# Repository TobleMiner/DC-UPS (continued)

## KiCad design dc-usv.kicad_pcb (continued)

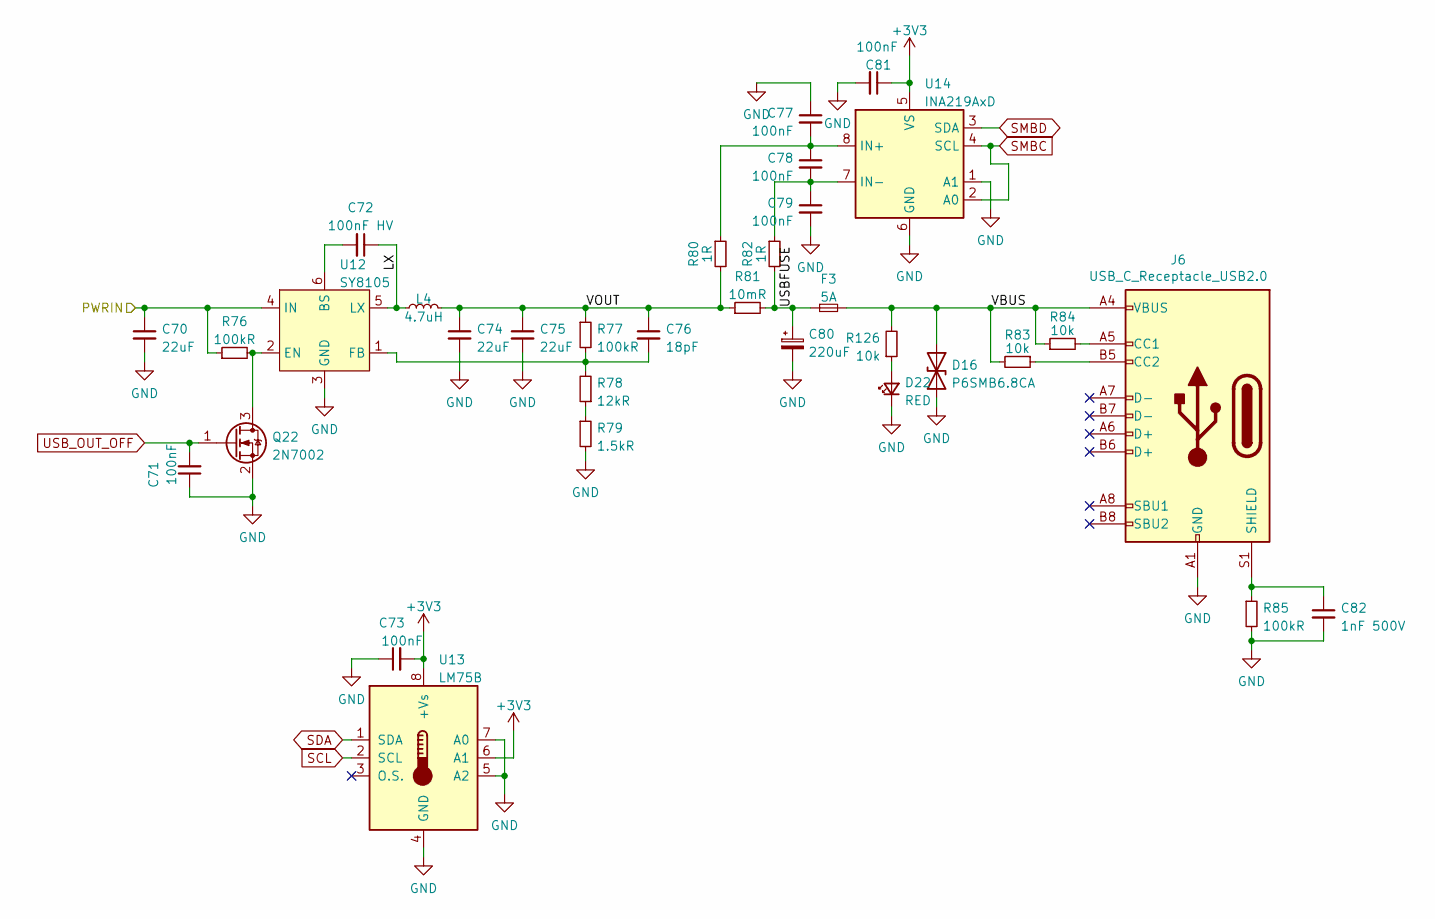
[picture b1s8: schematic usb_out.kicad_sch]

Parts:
C70, C74, C75: 22uF; C_0805_2012Metric; LCSC C602037
C71, C73, C77, C78, C79, C81: 100nF; C_0402_1005Metric; LCSC C1525
C72: 100nF HV; C_0603_1608Metric; LCSC C14663
C76: 18pF; C_0402_1005Metric; LCSC C1549
C80: 220uF; CP_Elec_6.3x7.7; LCSC C340768
C82: 1nF 500V; C_1206_3216Metric; LCSC C35216
D16: P6SMB6.8CA; D_SMB; LCSC C78395
D22: RED; LED_0603_1608Metric; LCSC C2286
F3: 5A; Fuse_1206_3216Metric; LCSC C377290
J6: USB_C_Receptacle_USB2.0; USB_C_Receptacle_Palconn_UTC16-G; LCSC C167321
L4: 4.7uH; L_Bourns_SRP7028A_7.3x6.6mm; LCSC C76857
Q22: 2N7002; SOT-23; LCSC C8545
R76, R77: 100kR; R_0402_1005Metric; LCSC C25741
R78: 12kR; R_0402_1005Metric; LCSC C25752
R79: 1.5kR; R_0402_1005Metric; LCSC C25867
R80, R82: 1R; R_0402_1005Metric; LCSC C25086
R81: 10mR; R_0805_2012Metric; LCSC C270927
R83, R84, R126: 10k; R_0402_1005Metric; LCSC C25744
R85: 100kR; R_1206_3216Metric; LCSC C17900
U12: SY8105; TSOT-23-6; LCSC C178247
U13: LM75B; MSOP-8_3x3mm_P0.65mm; LCSC C2837470
U14: INA219AxD; SOIC-8_3.9x4.9mm_P1.27mm; LCSC C138706

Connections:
/Charger/CS+: C70.1, R76.1, U12.4 (IN); also elsewhere on the board
/USB Output/LX: C72.1, L4.1, U12.5 (LX)
/USB Output/USBFUSE: C80.1, F3.1, R81.2, R82.2
/USB Output/VBUS: D16.1 (A1), F3.2, J6.A4 (VBUS), J6.A9 (VBUS), J6.B4 (VBUS), J6.B9 (VBUS), R83.2, R84.1, R126.2
/USB Output/VOUT: C74.1, C75.1, C76.1, L4.2, R77.1, R80.2, R81.1
unnamed: D22.2 (A), R126.1
unnamed: J6.A5 (CC1), R84.2
unnamed: J6.B5 (CC2), R83.1
unnamed: C82.1, J6.S1 (SHIELD), R85.1
unnamed: Q22.3 (D), R76.2, U12.2 (EN)
unnamed: R78.1, R79.1
unnamed: C72.2, U12.6 (BS)
unnamed: C76.2, R77.2, R78.2, U12.1 (FB)
unnamed: C77.2, C78.1, R80.1, U14.8 (IN+)
unnamed: C78.2, C79.1, R82.1, U14.7 (IN-)
SCL: U13.2 (SCL); also elsewhere on the board
SDA: U13.1 (SDA); also elsewhere on the board
SMBC: U14.2 (A0), U14.4 (SCL); also elsewhere on the board
SMBD: U14.3 (SDA); also elsewhere on the board
USB_OUT_OFF: C71.2, Q22.1 (G); also elsewhere on the board

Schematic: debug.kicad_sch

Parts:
C89: 1nF 500V; C_1206_3216Metric; LCSC C35216
C90, C91: 20pF; C_0402_1005Metric; LCSC C1554
C92, C93: 100nF; C_0402_1005Metric; LCSC C1525
D7: P6SMB6.8CA; D_SMB; LCSC C78395
J9: USB_C_Receptacle_USB2.0; USB_C_Receptacle_Palconn_UTC16-G; LCSC C167321
Q28, Q29: MMBT3904; SOT-23; LCSC C20526
R96: 100kR; R_1206_3216Metric; LCSC C17900
R97, R98: 5.1k; R_0402_1005Metric; LCSC C25905
R99, R100: 100R; R_0402_1005Metric; LCSC C25076
R101, R102: 100kR; R_0402_1005Metric; LCSC C25741
U16: CH340C; SOIC-16_3.9x9.9mm_P1.27mm; LCSC C84681
U18: SRV05-4; SOT-23-6; LCSC C85364
Y1: 12MHz (DNP); Crystal_SMD_3225-4Pin_3.2x2.5mm; LCSC C9002

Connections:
/Control Logic/EN: Q28.3 (C); also elsewhere on the board
/Control Logic/IO0: Q29.3 (C); also elsewhere on the board
/Control Logic/RXD: R99.1; also elsewhere on the board
/Control Logic/TXD: R100.2; also elsewhere on the board
unnamed: J9.A5 (CC1), R97.2
unnamed: J9.B5 (CC2), R98.1
unnamed: C89.1, J9.S1 (SHIELD), R96.1
unnamed: Q28.1 (B), R101.2
unnamed: Q28.2 (E), R102.1, U16.14 (~RTS)
unnamed: Q29.1 (B), R102.2
unnamed: Q29.2 (E), R101.1, U16.13 (~DTR)
unnamed: R100.1, U16.3 (RXD)
unnamed: R99.2, U16.2 (TXD)
unnamed: J9.A6 (D+), J9.B6 (D+), U16.5 (UD+), U18.4 (IO3)
unnamed: J9.A7 (D-), J9.B7 (D-), U16.6 (UD-), U18.6 (IO4)
unnamed: C90.2, U16.7 (XI), Y1.1
unnamed: C91.1, U16.8 (XO), Y1.3
VBUS: D7.2 (A2), J9.A4 (VBUS), J9.A9 (VBUS), J9.B4 (VBUS), J9.B9 (VBUS), U18.5 (VP); also elsewhere on the board

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
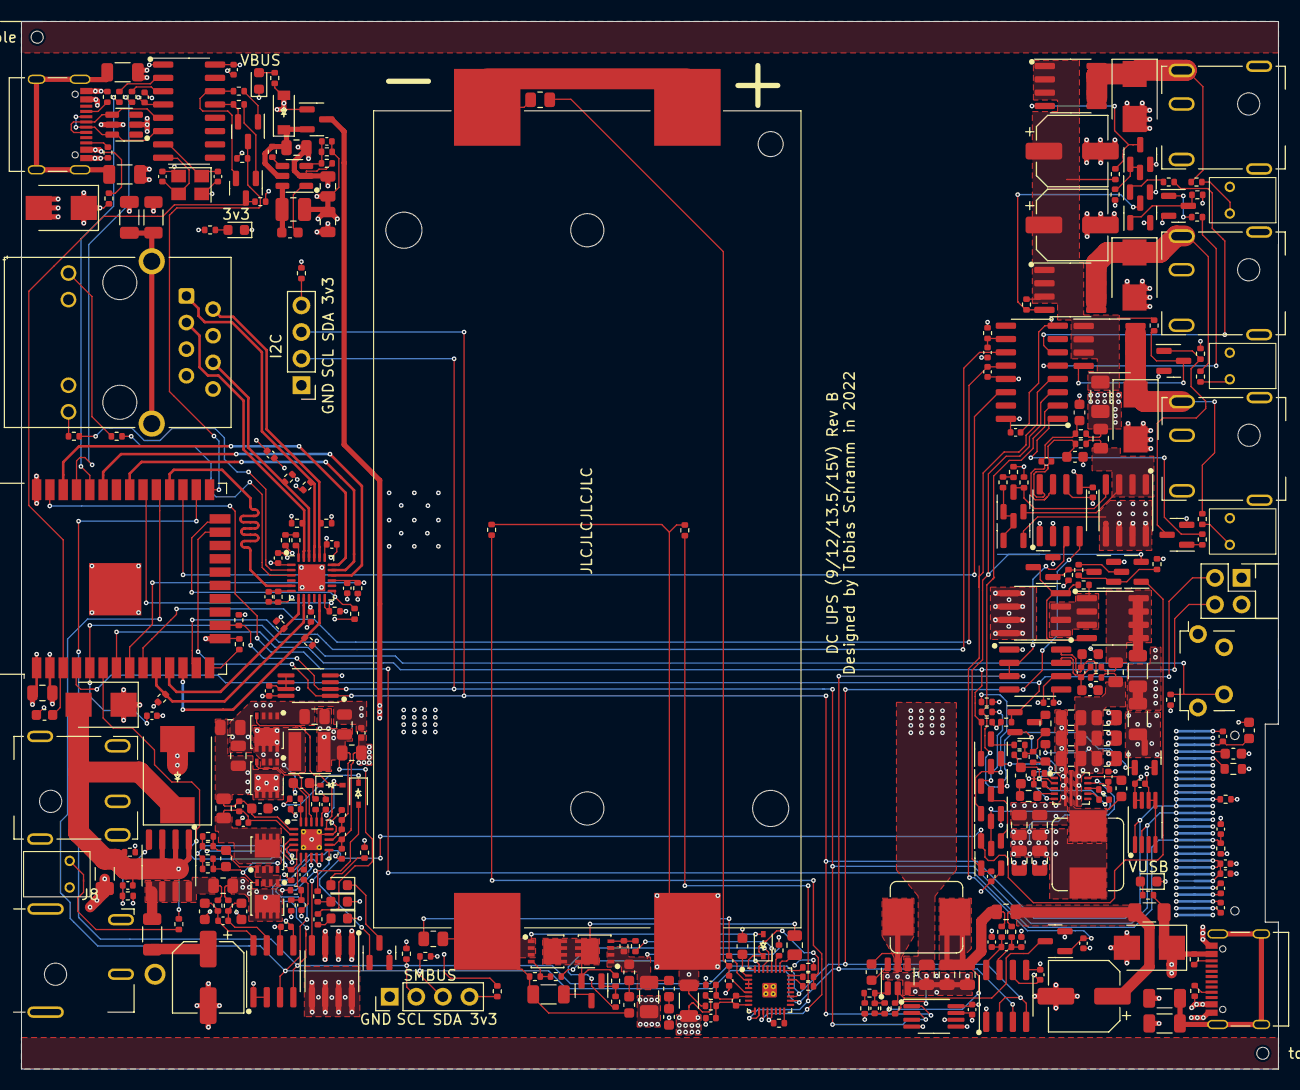
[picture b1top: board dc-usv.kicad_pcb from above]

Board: 4 copper layers, 120.0 x 100.0 mm, 342 parts (1 on the bottom side), 202 nets.

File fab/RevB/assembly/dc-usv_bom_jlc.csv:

"Comment","Designator","Footprint","LCSC Part #"
"100nF","C1,C2,C3,C4,C5,C13,C16,C24,C25,C26,C30,C42,C45,C47,C48,C51,C59,C65,C66,C68,C96,C99,C101,C71,C73,C77,C78,C79,C81,C86,C88,C92,C93","C_0402_1005Metric","C1525"
"2.2uF","C6,C53,C103","C_0603_1608Metric","C23630"
"100nF HV","C7,C8,C9,C10,C11,C14,C34,C41,C43,C44,C46,C54,C72,C85,C87","C_0603_1608Metric","C14663"
"1uF","C12,C17,C18,C27,C60,C62,C63,C64,C97,C98,C83","C_0402_1005Metric","C52923"
"100pF","C15,C67","C_0402_1005Metric","C1546"
"47nF HV","C19","C_0603_1608Metric","C1622"
"10uF","C20,C21,C22,C23,C35,C36,C37","C_0805_2012Metric","C15850"
"22uF","C28,C29,C31,C38,C39,C40,C94,C52,C55,C56,C57,C70,C74,C75","C_0805_2012Metric","C602037"
"4.7uF","C32","C_0402_1005Metric","C23733"
"680pF","C33","C_0603_1608Metric","C1630"
"220uF","C49,C50,C80,C84","CP_Elec_6.3x7.7","C340768"
"18pF","C58,C76","C_0402_1005Metric","C1549"
"470pF","C61","R_0402_1005Metric","C1537"
"1nF 500V","C69,C82,C89","C_1206_3216Metric","C35216"
"20pF","C90,C91","C_0402_1005Metric","C1554"
"10uF LV","C100","C_0402_1005Metric","C15525"
"4.7uF HV","C102","C_0603_1608Metric","C19666"
"22nF","C104,C95,C105","C_0402_1005Metric","C1532"
"1N4148WS","D1,D2,D3","D_SOD-323","C2128"
"BAV70","D4","SOT-23","C68978"
"SS36","D5","D_SMC","C35722"
"P6SMB18CA","D6,D9,D10,D11","D_SMB","C384916"
"RED","D8,D12,D13,D14","LED_Indicator_RED_MHK1373CRBDT","C417352"
"B5819W","D15","D_SOD-123","C8598"
"P6SMB6.8CA","D16,D7","D_SMB","C78395"
"YEL","D17,D21","LED_0603_1608Metric","C72038"
"RED","D18,D22","LED_0603_1608Metric","C2286"
"GRN","D19,D20","LED_0603_1608Metric","C72043"
"10A","F1","Fuse_1206_3216Metric","C242475"
"5A","F2,F3,F4","Fuse_1206_3216Metric","C377290"
"Output 2.0mm","J1,J2,J3","BarrelJack_2.0mm_DC-044B","C397334"
"HanRun_HR911105A","J5","RJ45_Hanrun_HR911105A","C12074"
"USB_C_Receptacle_USB2.0","J6,J9","USB_C_Receptacle_Palconn_UTC16-G","C167321"
"Input 2.0mm","J7","BarrelJack_2.0mm_DC-044B","C397334"
"Input 2.5mm","J8","BarrelJack_2.5mm_DC-044K-D025","C963204"
"2.2uH","L1","L_Taiyo-Yuden_MD-4040","C98361"
"1uH","L2","L_Bourns_SRP7028A_7.3x6.6mm","C439005"
"4.7uH","L3","L_1008_2520Metric","C91237"
"4.7uH","L4","L_Bourns_SRP7028A_7.3x6.6mm","C76857"
"AON7544","Q1,Q3,Q4,Q5","DFN-8-FET_3x3mm_P0.65mm","C315567"
"AO3401A","Q2,Q25","SOT-23","C15127"
"CSD17308Q3","Q6,Q7","DFN-8-FET_3x3mm_P0.65mm","C294987"
"AO4407A","Q8,Q10,Q19,Q21,Q23,Q32,Q35,Q38","SOIC-8_3.9x4.9mm_P1.27mm","C167517"
"MMBT5401","Q9,Q24","SOT-23","C8326"
"MMBT3904","Q12,Q18,Q28,Q29,Q30,Q33,Q36","SOT-23","C20526"
"2N7002","Q26,Q11,Q13,Q14,Q15,Q16,Q17,Q20,Q22,Q31,Q34,Q37","SOT-23","C8545"
"1mR","R1","R_1206_3216Metric","C76287"
"100R","R2,R3,R130,R69,R122,R123,R99,R100","R_0402_1005Metric","C25076"
"100R 0805","R4,R5,R11","R_0805_2012Metric","C17408"
"10MR","R6,R10,R13","R_0402_1005Metric","C26082"
"300R","R7,R47,R48","R_1206_3216Metric","C17887"
"5.1k","R8,R9,R12,R18,R22,R120,R124,R125,R97,R98","R_0402_1005Metric","C25905"
"10k","R14,R95,R128,R129,R20,R119,R121,R93,R51,R53,R56,R57,R58,R60,R61,R62,R63,R65,R118,R127,R132,R83,R84,R126,R103,R113,R114,R115","R_0402_1005Metric","C25744"
"100kR","R15,R26,R27,R29,R31,R33,R35,R41,R46,R49,R50,R131,R52,R54,R59,R74,R116,R76,R77,R86,R87,R101,R102,R104,R105,R106,R107,R108,R109,R110,R111,R112","R_0402_1005Metric","C25741"
"39kR","R16","R_0402_1005Metric","C25783"
"18kR","R17,R21","R_0402_1005Metric","C25762"
"10mR","R19,R25,R42,R43,R81,R90","R_0805_2012Metric","C270927"
"10R","R23,R24","R_0402_1005Metric","C25077"
"150k","R28","R_0402_1005Metric","C25755"
"56kR","R30,R92","R_0402_1005Metric","C25796"
"47kR","R32","R_0603_1608Metric","C25819"
"180kR","R34","R_0603_1608Metric","C22827"
"220kR","R36","R_0402_1005Metric","C25767"
"1R","R37,R38,R44,R45,R80,R82,R89,R91","R_0402_1005Metric","C25086"
"750kR","R39","R_0603_1608Metric","C23240"
"15kR","R40","R_0402_1005Metric","C25756"
"22kR","R55","R_0402_1005Metric","C25768"
"1.5kR","R64,R79","R_0402_1005Metric","C25867"
"50R","R66,R68,R70,R71","R_0402_1005Metric","C25120"
"12kR","R67,R78","R_0402_1005Metric","C25752"
"330R","R72,R73","R_0402_1005Metric","C25104"
"100kR","R75,R85,R96","R_1206_3216Metric","C17900"
"10R","R88","R_1206_3216Metric","C17903"
"390kR","R117","R_0603_1608Metric","C23150"
"SW_DIP_x02","SW1","PinHeader_2x02_P2.54mm_Vertical","C692490"
"SW_Push","SW2","x-1825027-x","C266183"
"10k","TH1,TH2","R_0402_1005Metric","C279801"
"BQ40z50-R2","U1","VQFN-32-4.1x4.1-EP-1.4","C179743"
"LM75B","U2,U7,U13","MSOP-8_3x3mm_P0.65mm","C2837470"
"BQ24715","U3","QFN-20-1EP_3.5x3.5mm_P0.5mm_EP2x2mm_ThermalVias","C276341"
"TPS61178x","U4","VSON-HR-13","C127918"
"INA219AxD","U5,U6,U14,U15","SOIC-8_3.9x4.9mm_P1.27mm","C138706"
"SY8120B1ABC","U8","SOT-23-6","C88474"
"ESP32-WROOM-32E","U9","ESP32-WROOM-32","C701342"
"LAN8720A","U10","QFN-24-1EP_4x4mm_P0.5mm_EP2.6x2.6mm","C45223"
"74HC595","U11","SOIC-16_3.9x9.9mm_P1.27mm","C5947"
"SY8105","U12","TSOT-23-6","C178247"
"CH340C","U16","SOIC-16_3.9x9.9mm_P1.27mm","C84681"
"N066-6448TSWEG03-H28","U17","N066-6448TSWEG03-H28","C2890608"
"SRV05-4","U18","SOT-23-6","C85364"

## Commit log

2022-09-19 Add partial DC output circuitry
2022-09-20 Finish DC output schematic capture
2022-09-20 Add barrel jack footprints
2022-09-20 Add individually switchable outputs
2022-09-21 Charger and step-down component placement
2022-09-21 Partial DC out step-up component placement
2022-09-21 Finish step-up component placement and partial layout
2022-09-21 Add 64x48 SSD1306 OLED
2022-09-22 Plan front panel element positioning
2022-09-23 Partial layout
2022-09-23 Partial DC out component placement
2022-09-25 Finish initial layout
2022-09-25 Add debouncing capacitor to front panel button
2022-09-25 Optimize power routing
2022-09-25 Add SMBUS and I2C debug headers
2022-09-25 Hide silkscreen designators
2022-09-25 Thermal optimizations
2022-09-25 Add component direction indicators
2022-09-25 Add tooling holes
2022-09-25 Add thermal plane to SYSPWR MOSFET
2022-09-25 Optimize thermal connectivity of USB output regulator
2022-09-25 Add informational silkscreen designators
2022-09-25 Add more voltage rail LEDs
2022-09-25 Fix DRC errors
2022-09-25 Fix footprint origins for JLC assembly
2022-09-25 Adjust RMII clock to average electrical RMII signal length
2022-09-25 Swap GPIO2 and GPIO23 to ensure UART download mode can be entered
2022-09-25 Move front panel button further to PCB center
    Makes sure button does not stick out quite as far from front panel
2022-09-25 Fix embarrassing typo
2022-09-26 Fix incorrect part number on R32
    Previously chosen part had 0402 footprint, 0603 needed.
2022-09-27 Add frontpanel
2022-09-28 Add backpanel
2022-09-28 Add 3d models
2022-10-10 Fix reversed debug USB TVS
2022-10-16 Add FUSE pulldown and PTC dummy
    In contrast to documentation provided by TI FUSE is neither just an
    output nor does the PTCEN feature work as advertised.
    The FUSE pin contains a switchable 150nA current source. Presumably it
    is used as a safety to detect if the FUSE pin is open. Unfortunately the
    gauage will not allow control of the CHG, DSG and PRECHG FETs when it
    detects an open FUSE pin. There does not seem to be any configuration
2022-10-16 Fix gate discharge resistor on Q10
    The gate discharge resistor on Q10 was by mistake connected to drain
    instead of source.
2022-10-16 Add ase discharge resistor to Q18
2022-10-16 Fix swapped gauage current sense pins
2022-10-16 Compensate leakage through VBUS schottky diode
    Add 10k resistor from VBUS to GND to compensate for schottky diode
    leakage.
2022-10-17 Add missing annotations
2022-10-17 Fix incorrect AO447A partnumber
    The previous partnumber was pointing to a N-Channel MOSFET.
    Use a P-Channel one.
2023-06-03 Rev 1.0 bugfixes
    Changes:
    - Replace DCOK-driven DC passthrough switch with ideal diode
    - Reduce INA219 series filter resistance to 1 ohm
    - Simplify debug USB power gating
    - Fix incorrect USB CC pullups
2023-07-01 Sync PCB with schematic
2023-07-01 Add minimal readme
2023-07-01 Add LICENSE
2023-07-01 Add RevB fabrication files
2023-07-01 Add more details to assembly section of readme
2023-09-08 Fix incorrectly referenced FET footprint library
2024-05-09 lib: update JLCPCB tooling footprints
    Add fiducials and mouse bites
2024-05-09 Ignore lockfiles
2024-05-09 Add RevC fabrication files
2024-05-09 Fix remaining RevB bugs
    - DNP Q13 by default to ensure uninterrupted power power delivery
    - Use lower resistance load resistors for DC step-up selftest
    - Add edge rails to support JLCPCB standard assembly
    Unfortuantely JLCPCB does not seems to offer ESP32 WROOMs anymore for
    economic PCBA. Thus edge-rails have been added to support standard PCBA.
2024-05-09 Fix aluminum case part number
